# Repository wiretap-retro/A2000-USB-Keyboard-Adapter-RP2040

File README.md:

# A2000 USB Keyboard Adapter RP2040
A USB keyboard adapter for the Amiga 2000 based on the Pi Stamp RP2040

## Intro
This is a USB keyboard adapter I designed a board for to use in the Amiga 2000. It is based on the amigahid-pico firmware by borb (nine), as well as my other A500 USB adapter. The KiCAD files, Gerbers, and BOM are in this repository. The completed board attaches to the CIA socket and provides a USB inputs for your interface device.

## Parts
* PCB: PCB's can be ordered from JLCPCB by uploading the Gerber files, but any PCB house should be able to make these since it is a simple/small design. (PCBway, OSH Park, AllPCB, etc.)
* Pi Stamp RP2040: https://shop.pimoroni.com/products/rp2040-stamp
* All other PCB mounted components were sourced at Mouser per the BOM. Other sources for the components could be Digikey, Farnell, RS, etc. depending on what is available in your location. Chip/component shortages may impact your ability to get everything all in one place. Substitutions may need to be made.
* You will need to find a pin header to USB cable that suits your case needs, or a USB PCI bracket, possibly with an extension. (Amazon, Ebay, Aliexpress, etc.)

## Building the Adapter
* Solder the smallest SMD components first. (resistors, capacitors, logic level shifter, MicroUSB connector)
* Solder the right angle pin connector. (USB header)
* Solder the Pi Stamp RP2040 into place. You can solder directly onto the board, or optionally use the male and female headers to socket mount it. I recommend using the male and female pin headers so you can easily pull the RP2040 out if you need to use it again in the future on another project.
* Solder the USB type-A connector.
* Solder the vertical USB_BOOT header and reset pin into place. You can skip the reset pin if you're soldering a wire directly to the board instead.
* Solder the two 20-pin machine pin headers to the bottom of the PCB.
* Solder the 40-pin DIP socket.
* I recommend checking all solder joints under magnification to ensure everything is connected with no shorts.

## Flashing the Firmware
First off, a huge thank you to Nine for developing the amigahid-pico, as this design uses its firmware. Firmware is located at: https://github.com/borb/amigahid-pico/
1. Build the firmware per the instructions at https://github.com/borb/amigahid-pico/blob/main/doc/installation.md
2. Place a jumper on the USB_BOOT pin.
3. Plug a MicroUSB cable to the PCB's MicroUSB port and plug the other end into the PC you just compiled the firmware on. It will then show up as a mass storage device.
4. Remove the jumper from the USB_BOOT pin.
5. Copy the amigahid-pico.uf2 file from the "build/src/" directory you compiled to the RP2040's mounted USB storage volume. It will then disconnect/reset.
6. Disconnect the USB cable from the PC and keyboard adapter PCB.

## Installation into the Amiga
1. Gain access to your Amiga 2000 motherboard. This will require removing the top lid, as well as the PSU/3.5/5.25 mezzanine chassis.
2. Remove the U300 CIA chip and install the keyboard adapter board into its place, paying attention to orientation.
3. Plug the CIA chip into the DIP socket of the keyboard adapter, paying attention to orientation.
4. Plug your USB cable into the pin header, or USB cable into the USB type-A port.
5. Install the USB bracket into a spare ISA/Zorro slot.
6. Connect a wire from the Reset pin on the keyboard adapter PCB to Gary chip Pin #5. I find that a small spring loaded test lead works best for easy install/removal. 
7. Plug the keyboard or wireless keyboard adapter into the newly installed USB port at the rear of the A2000.
8. Boot the Amiga and test it out!

## Optional Stuff
* USB HID mouse support is included in Nine's firmware, but none of the mice I used would work with the A500 adapter which is nearly identical in terms of design. I use a DB9 connected OpenLaserMouse anyway, but maybe you'll have better luck testing various mice to see if one works. I know the firmware is still an in-progress project, or maybe I didn't do something right when I compiled the firmware. 
* Amiga keys are currently mapped to right and left windows keys. Before compiling the firmware, you can modify those keys if necessary at your own discretion.
* Reset is initiated by Left Ctrl + Left Win + Right Win (CTRL + AMIGA + AMIGA)

## Miscellaneous
This board is provided as-is and open source. This project is tested and working. It does not provide firmware and relies on a different project for the firmware as linked above. Review the design and build/test at your own risk.
If you plan to sell this board, firmware is per the license at: https://github.com/borb/amigahid-pico/

## Revisions
* Rev 2 - Latest, fixed floating ground on the level shift logic.
* Rev 1 - Adjust layout of chips and ports. Depreciated.
* Rev 0 - Initial / Depreciated.

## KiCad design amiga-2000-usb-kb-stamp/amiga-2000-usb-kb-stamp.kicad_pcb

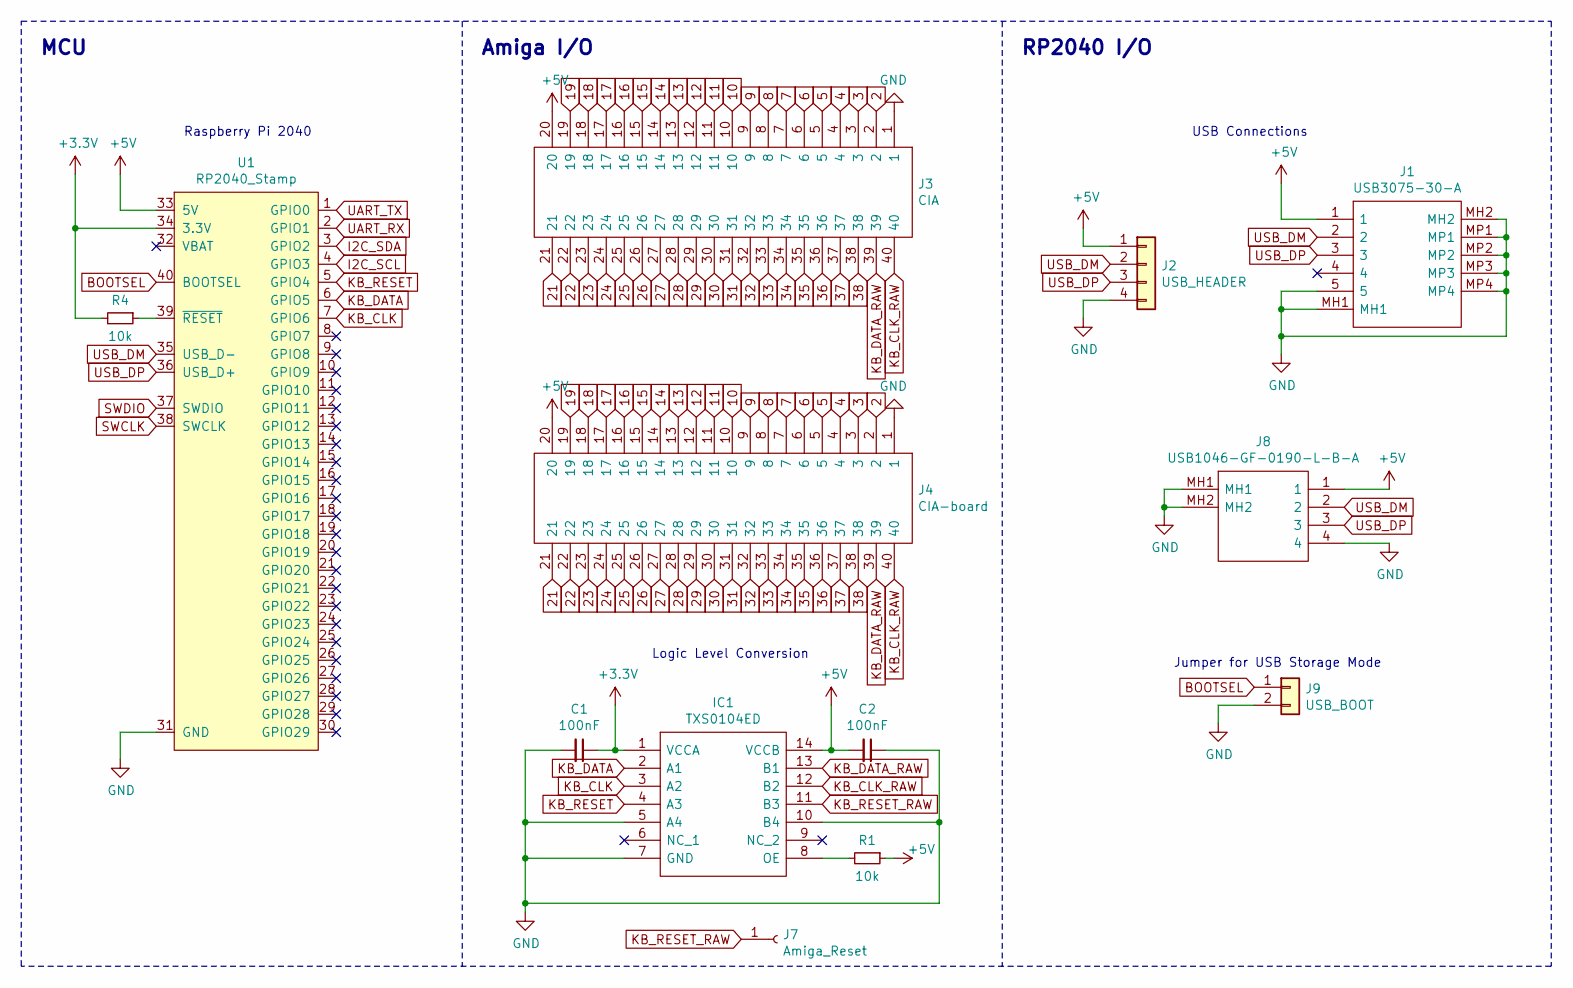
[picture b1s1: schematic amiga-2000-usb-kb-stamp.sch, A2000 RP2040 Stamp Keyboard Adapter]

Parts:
C1, C2: 100nF; C_0805_2012Metric_Pad1.15x1.40mm_HandSolder
IC1: TXS0104ED; SOIC127P600X175-14N; Mouser Part Number 595-TXS0104ED
J1: USB3075-30-A; USB307530A; Mouser Part Number 640-USB3075-30-A
J2: USB_HEADER; PinHeader_1x04_P2.54mm_Horizontal
J3: CIA; DIPS1544W70P254L5080H530Q40N; Mouser Part Number 571-1-2199299-5
J4: CIA-board; DIPS1544W70P254L5080H530Q40N; Mouser Part Number 571-1-2199299-5
J7: Amiga_Reset; PinHeader_1x01_P2.54mm_Vertical
J8: USB1046-GF-0190-L-B-A; USB1046GF0190LBA; Mouser Part Number 640-USB1046GF0190LBA
J9: USB_BOOT; PinHeader_1x02_P2.54mm_Vertical
R1, R4: 10k; R_0805_2012Metric_Pad1.15x1.40mm_HandSolder
U1: RP2040_Stamp; RP2040_Stamp_THT

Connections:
2: J3.2, J4.2
3: J3.3, J4.3
4: J3.4, J4.4
5: J3.5, J4.5
6: J3.6, J4.6
7: J3.7, J4.7
8: J3.8, J4.8
9: J3.9, J4.9
10: J3.10, J4.10
11: J3.11, J4.11
12: J3.12, J4.12
13: J3.13, J4.13
14: J3.14, J4.14
15: J3.15, J4.15
16: J3.16, J4.16
17: J3.17, J4.17
18: J3.18, J4.18
19: J3.19, J4.19
21: J3.21, J4.21
22: J3.22, J4.22
23: J3.23, J4.23
24: J3.24, J4.24
25: J3.25, J4.25
26: J3.26, J4.26
27: J3.27, J4.27
28: J3.28, J4.28
29: J3.29, J4.29
30: J3.30, J4.30
31: J3.31, J4.31
32: J3.32, J4.32
33: J3.33, J4.33
34: J3.34, J4.34
35: J3.35, J4.35
36: J3.36, J4.36
37: J3.37, J4.37
38: J3.38, J4.38
+3V3: C1.1, IC1.1 (VCCA), R4.2, U1.34 (3.3V)
+5V: C2.2, IC1.14 (VCCB), J1.1, J2.1, J3.20, J4.20, J8.1, R1.1, U1.33 (5V)
BOOTSEL: J9.1, U1.40 (BOOTSEL)
GND: C1.2, C2.1, IC1.5 (A4), IC1.7 (GND), IC1.10 (B4), J1.5, J1.MH1, J1.MH2, J1.MP1, J1.MP2, J1.MP3, J1.MP4, J2.4, J3.1, J4.1, J8.4, J8.MH1, J8.MH2, J9.2, U1.31 (GND)
I2C_SCL: U1.4 (GPIO3)
I2C_SDA: U1.3 (GPIO2)
KB_CLK: IC1.3 (A2), U1.7 (GPIO6)
KB_CLK_RAW: IC1.12 (B2), J3.40, J4.40
KB_DATA: IC1.2 (A1), U1.6 (GPIO5)
KB_DATA_RAW: IC1.13 (B1), J3.39, J4.39
KB_RESET: IC1.4 (A3), U1.5 (GPIO4)
KB_RESET_RAW: IC1.11 (B3), J7.1
unnamed: IC1.8 (OE), R1.2
unnamed: R4.1, U1.39 (~RESET)
SWCLK: U1.38 (SWCLK)
SWDIO: U1.37 (SWDIO)
UART_RX: U1.2 (GPIO1)
UART_TX: U1.1 (GPIO0)
USB_DM: J1.2, J2.2, J8.2, U1.35 (USB_D-)
USB_DP: J1.3, J2.3, J8.3, U1.36 (USB_D+)

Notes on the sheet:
Jumper for USB Storage Mode
Logic Level Conversion
Raspberry Pi 2040
MCU
Amiga I/O
RP2040 I/O
USB Connections

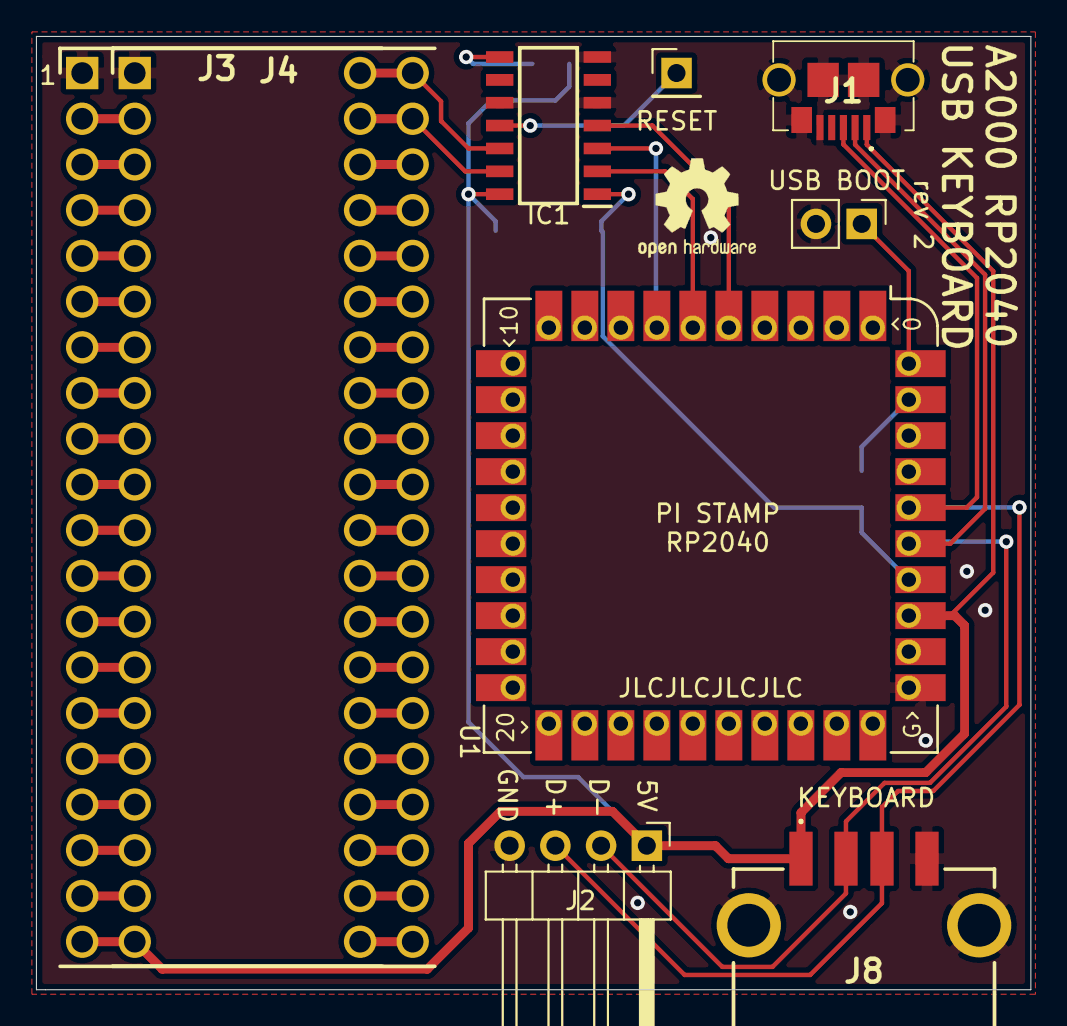
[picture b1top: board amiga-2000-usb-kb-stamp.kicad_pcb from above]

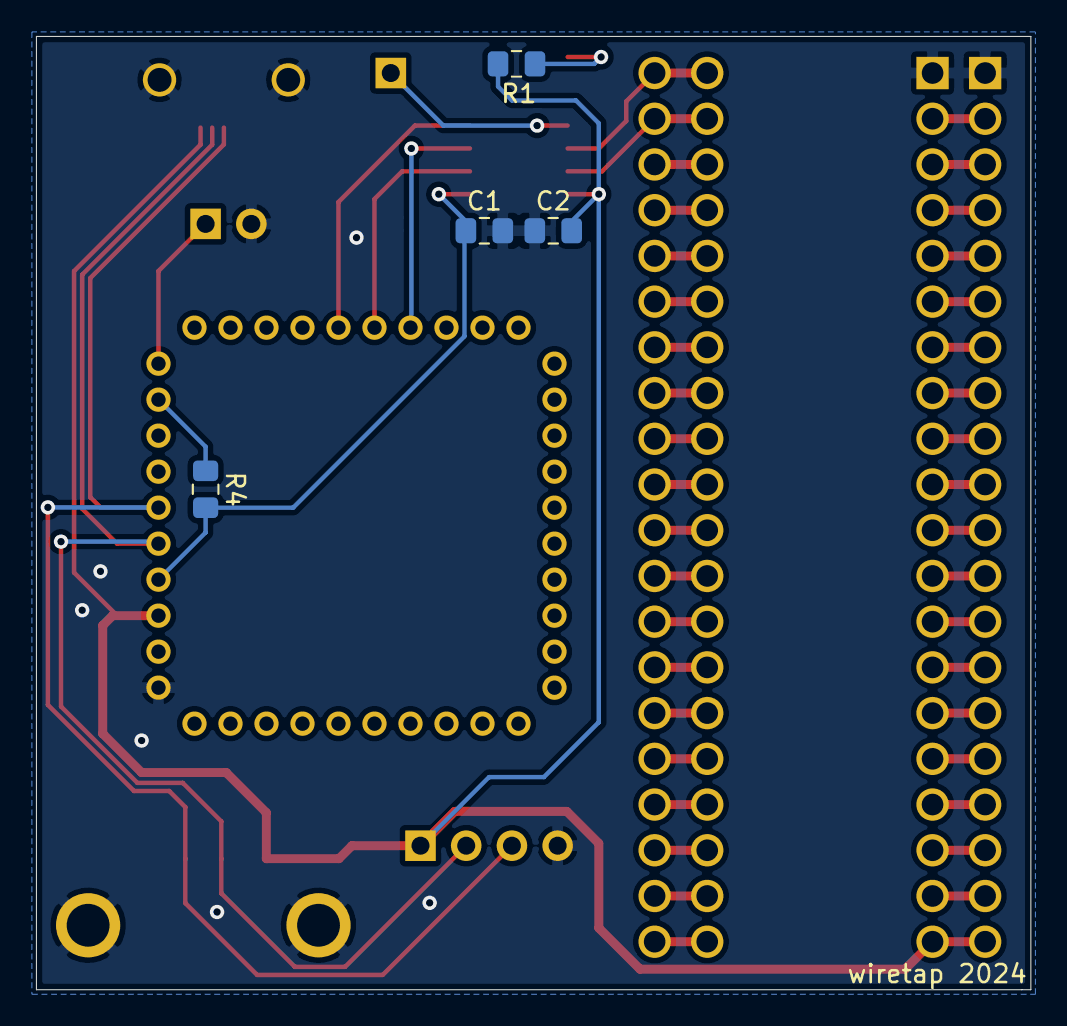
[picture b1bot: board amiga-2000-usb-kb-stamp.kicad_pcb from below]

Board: 2 copper layers, 55.2 x 53.0 mm, 13 parts (4 on the bottom side), 50 nets.

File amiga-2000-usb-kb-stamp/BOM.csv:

Reference, Quantity, Value, Footprint, Description, Manufacturer_Name, Manufacturer_Part_Number, Mouser Part Number
C1 C2 ,2,100nF,Capacitor_SMD:C_0805_2012Metric_Pad1.15x1.40mm_HandSolder,,,,
IC1 ,1,TXS0104ED,SOIC127P600X175-14N,"TXS0104ED, Voltage Level Translator, Open Drain 1.65 to 3.6, 2.3 to 5.5V 14-Pin SOIC",Texas Instruments,TXS0104ED,595-TXS0104ED
J1 ,1,USB3075-30-A,USB307530A,"GCT (GLOBAL CONNECTOR TECHNOLOGY) - USB3075-30-A - USB Connector, Micro USB Type B, USB 2.0, Receptacle, 5 Ways, Surface Mount, Right Angle",GCT (GLOBAL CONNECTOR TECHNOLOGY),USB3075-30-A,640-USB3075-30-A
J2 ,1,USB_HEADER,Connector_PinHeader_2.54mm:PinHeader_1x04_P2.54mm_Horizontal,,,,
J3 ,1,CIA,DIPS1544W70P254L5080H530Q40N,"TE CONNECTIVITY - 1-2199299-5 - IC SOCKET, DIP, 40POS, TH",TE Connectivity,1-2199299-5,571-1-2199299-5
J4 ,1,CIA-board,,"Use machine pin header, 2 of each, 1x20 2.54mm, solder to bottom side",,,
J7 ,1,Amiga_Reset,Connector_PinHeader_2.54mm:PinHeader_1x01_P2.54mm_Vertical,,,,
J8 ,1,USB1046-GF-0190-L-B-A,USB1046GF0190LBA,"USB Connectors USB A Skt, Top Mount, SMT, R/A, GF, Black, With 1.9mm shell stake, T&R",GCT (GLOBAL CONNECTOR TECHNOLOGY),USB1046-GF-0190-L-B-A,640-USB1046GF0190LBA
J9 ,1,USB_BOOT,Connector_PinHeader_2.54mm:PinHeader_1x02_P2.54mm_Vertical,,,,
R1 R4 ,2,10k,Resistor_SMD:R_0805_2012Metric_Pad1.15x1.40mm_HandSolder,,,,
U1 ,1,RP2040_Stamp,SamacSys_Parts:RP2040_Stamp_THT,https://shop.pimoroni.com/products/rp2040-stamp?variant=3956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,,,

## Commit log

2022-09-08 Added files via upload
    Inital rev 0
2022-09-08 Uploaded picture of PCB
    Rev 0
